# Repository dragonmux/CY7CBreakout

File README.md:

# CY7CBreakout

CY7CBreakout is a breadboard-compatible Cypress CY7C68013A breakout board.

This project is licensed under the CERN OHL v.1.2 or later.

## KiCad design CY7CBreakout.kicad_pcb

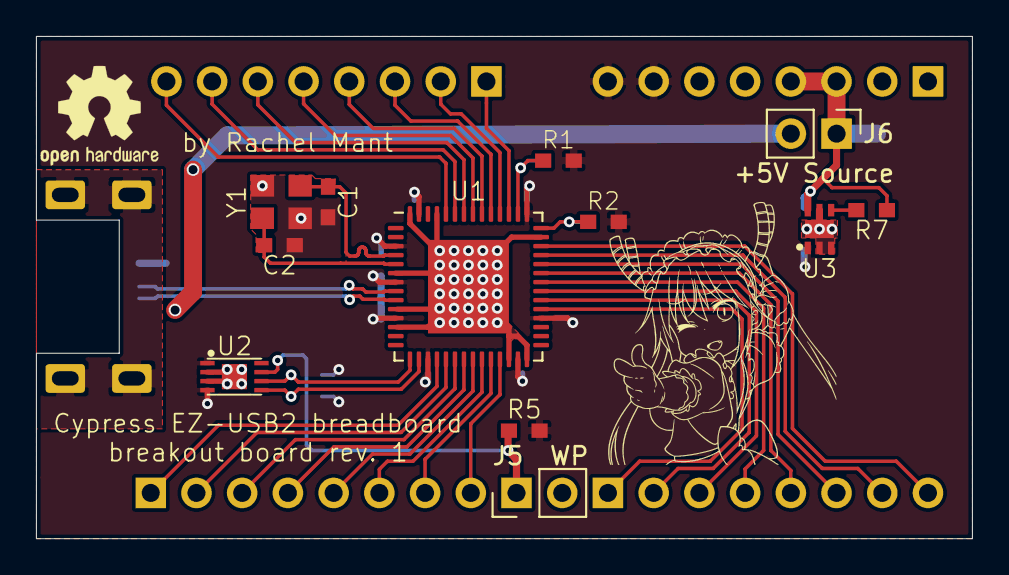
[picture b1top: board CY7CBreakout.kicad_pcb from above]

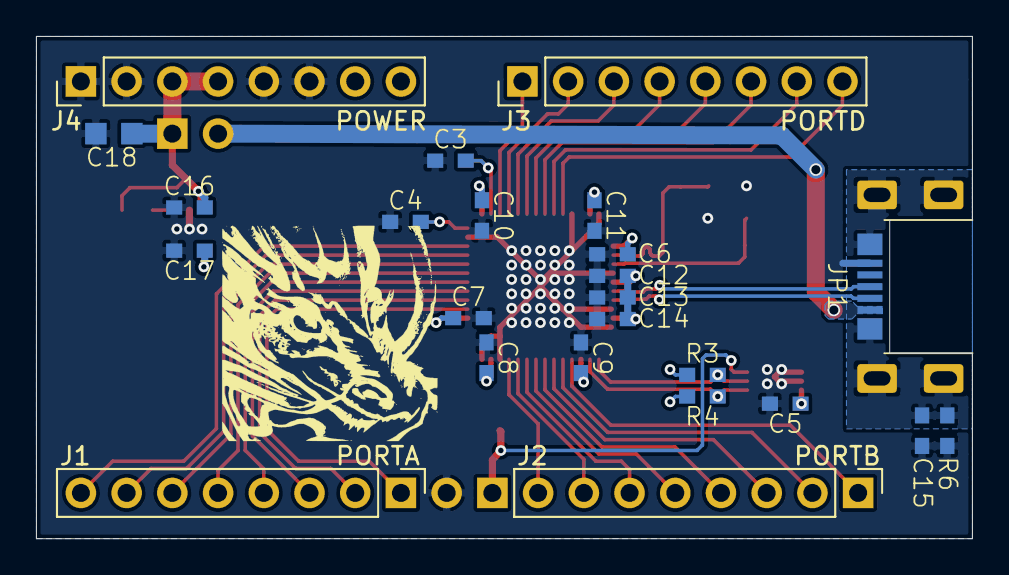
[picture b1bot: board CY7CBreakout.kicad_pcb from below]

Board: 2 copper layers, 52.0 x 27.9 mm, 39 parts (25 on the bottom side), 39 nets.

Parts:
C1, C2: 15pF; C0603
C3, C4: 10uF; C0603
C5, C6, C7, C8, C9, C10, C11, C15: 0.1uF; C0603
C12: 0.22uF; C0603
C13: 10nF; C0603
C14: 1nF; C0603
C16, C17: 4.7uF; C0603
C18: 47uF; C0805
DRG1: トール; トール-12.9x14.8
DRG2: Nagadreth; Nagadreth-12.0x12.0
J1: PORTA; PinHeader_1x08_P2.54mm_Vertical
J2: PORTB; PinHeader_1x08_P2.54mm_Vertical
J3: PORTD; PinHeader_1x08_P2.54mm_Vertical
J4: POWER; PinHeader_1x08_P2.54mm_Vertical
J5: WP; PinHeader_1x02_P2.54mm_Vertical
J6: +5V Source; PinHeader_1x02_P2.54mm_Vertical
JP1: USB-Micro-B; MICRO-USB-B-(IN_PCB)
LOGO1: Logo_Open_Hardware_Small; OSHW-Logo2_7.3x6mm_SilkScreen
R1, R7: 100k; R0603
R2, R5: 10k; R0603
R3, R4: 2k2; R0603
R6: 1M; R0603
U1: CY7C68013A-56LTX; QFN-56-1EP_8x8mm_P0.5mm_EP4.5x5.2mm
U2: M24128; UFDFPN8
U3: TLV755P; DFN6-2x2mm
Y1: 24MHz; SMD2520

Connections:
+3V3: C5.1, C6.1, C7.1, C8.1, C9.1, C10.1, C11.1, C12.1, C13.1, C14.1, C17.1, J4.7, J4.8, R1.1, R2.1, R3.1, R4.1, R5.2, U1.3, U1.7, U1.11, U1.17, U1.27, U1.32, U1.43, U1.55, U2.1, U2.4, U3.1
+5V: C16.2, C18.1, J4.3, J4.4, J6.1, R7.2, U3.6
/Breadboard Connectors/PA0: J1.1, U1.33
/Breadboard Connectors/PA1: J1.2, U1.34
/Breadboard Connectors/PA2: J1.3, U1.35
/Breadboard Connectors/PA3: J1.4, U1.36
/Breadboard Connectors/PA4: J1.5, U1.37
/Breadboard Connectors/PA5: J1.6, U1.38
/Breadboard Connectors/PA6: J1.7, U1.39
/Breadboard Connectors/PA7: J1.8, U1.40
/Breadboard Connectors/PB0: J2.1, U1.18
/Breadboard Connectors/PB1: J2.2, U1.19
/Breadboard Connectors/PB2: J2.3, U1.20
/Breadboard Connectors/PB3: J2.4, U1.21
/Breadboard Connectors/PB4: J2.5, U1.22
/Breadboard Connectors/PB5: J2.6, U1.23
/Breadboard Connectors/PB6: J2.7, U1.24
/Breadboard Connectors/PB7: J2.8, U1.25
/Breadboard Connectors/PD0: J3.1, U1.45
/Breadboard Connectors/PD1: J3.2, U1.46
/Breadboard Connectors/PD2: J3.3, U1.47
/Breadboard Connectors/PD3: J3.4, U1.48
/Breadboard Connectors/PD4: J3.5, U1.49
/Breadboard Connectors/PD5: J3.6, U1.50
/Breadboard Connectors/PD6: J3.7, U1.51
/Breadboard Connectors/PD7: J3.8, U1.52
/Processor+USB/D+: JP1.D+, U1.8
/Processor+USB/D-: JP1.D-, U1.9
/Processor+USB/OSC+: C1.1, U1.4, Y1.1
/Processor+USB/OSC-: C2.1, U1.5, Y1.3
/Processor+USB/SCL: R3.2, U1.15, U2.6
/Processor+USB/SDA: R4.2, U1.16, U2.5
/Processor+USB/VBUS: J6.2, JP1.VCC
/Processor+USB/WAKEUP: C3.1, R1.2, U1.44
/Processor+USB/~RESET: C4.1, R2.2, U1.42
/Supply + Support Elements/EEPROM_WC: J5.1, R5.1, U2.7
Earth: C15.1, JP1.SHIELD, R6.2
GND: C1.2, C2.2, C3.2, C4.2, C5.2, C6.2, C7.2, C8.2, C9.2, C10.2, C11.2, C12.2, C13.2, C14.2, C15.2, C16.1, C17.2, C18.2, J4.1, J4.2, J4.5, J4.6, J5.2, JP1.GND1, R6.1, U1.6, U1.10, U1.12, U1.26, U1.28, U1.41, U1.53, U1.56, U1.57, U2.2, U2.3, U2.GND, U3.2, U3.3, U3.5, U3.GND, Y1.2, Y1.4
unnamed: R7.1, U3.4

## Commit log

2020-07-05 Added the board and schematics for the breakout board
2020-07-05 Added an ignore for all the *-bak files KiCAD makes
2020-07-05 Added the KiCAD project to the repo
2020-07-05 Added licensing and a bare-bones README
2020-07-05 Added the OSHW logo to the silkscreen for the board
2020-07-05 Fixed all the silkscreen issues
2020-07-05 Fixed a couple more silkscreen locations which were off
2020-07-10 Done some necessary cleanup of the PCB silkscreen to get the right result from running the gerbers
2020-07-10 Added some PCB art in the form of Tohru and Nagadreth
2020-07-10 Added gerbers and symlinks to make them manufacturer friendly
2020-07-10 Added the Creators Covenant Code of Conduct to the repo
2020-07-12 Added a note to the board that this is the first revision, in case additional revisions end up being made
2020-07-12 Regenerated the gerbers to reflect the last commit
